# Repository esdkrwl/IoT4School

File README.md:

# IoT4School 2.0
Eine exemplarische Internet of Things Infrastruktur für den Einsatz im Informatikunterricht.

Die größten Änderungen zur Version 1.0:
- Verwendung von Micropython (basierend auf Python 3.4) anstatt Arduino (C++)
- Verwendung eines modularen Stecksystems auf Basis des Evaluationsboards Wemos D1 (ESP8266)
- Blockbasierte Einrichtung und Programmierung der Module mittels BIPES

Hardwarevoraussetzungen:
- Raspberry Pi 3b mit einer mindestens 16GB großen microSD Karte (Raspberry Pi OS: Buster)
  - Möglicherweise auch kompatibel zum Raspberry Pi 4, jedoch nicht getestet
- Ein WLAN-Router zum Empfangen und Versenden von Netzwerkpaketen
- [Wemos D1 mini][1] Mikrocontroller sowie (Wemos-kompatible) [Shields][2]

Um das Projekt IoT4School 2.0 nutzen zu können, müssen folgende Anleitungen nach Reihenfolge durchgeführt werden:  
- [Raspberry Einrichtung mit Image [Für Einsteigende]][3] **ODER** [Raspberry Einrichtung ohne Image [Für erfahrene Anwendende]][4]
- [Wemos D1 Mini Ersteinrichtung und Konfiguration][5]
- [Einführung in das blockbasierte Programmieren mit BIPES und Node-RED][6]

Zusätzlich werden den Entwickelnden zur Erweiterung der IoT4School-Infrastruktur folgende Anleitungen zur Verfügung gestellt:
- [Blöcke für IoT4School entwickeln und einbinden][7]
- [Anpassungen an der Micropython-Firmware vornehmen][8]

Weitere Informationen zum Projekt sind im [Wiki](https://github.com/esdkrwl/IoT4School/wiki) zu finden.

[1]: https://www.wemos.cc/en/latest/d1/d1_mini.html
[2]: https://www.wemos.cc/en/latest/d1_mini_shield/index.html
[3]: https://github.com/esdkrwl/IoT4School/wiki/Raspberry-Pi-Einrichtung-mit-Image
[4]: https://github.com/esdkrwl/IoT4School/wiki/Raspberry-Pi-Einrichtung-ohne-Image
[5]: https://github.com/esdkrwl/IoT4School/wiki/Wemos-D1-mini-(ESP8266)-Einrichtung
[6]: https://github.com/esdkrwl/IoT4School/wiki/Einf%C3%BChrung-in-das-blockbasierte-Programmieren-mit-BIPES-und-Node-RED
[7]: https://github.com/esdkrwl/IoT4School/wiki/Erstelle-IoT4School-2.0-Bl%C3%B6cke
[8]: https://github.com/esdkrwl/IoT4School/wiki/Erzeugen-einer-eigenen-MicroPython-Firmware

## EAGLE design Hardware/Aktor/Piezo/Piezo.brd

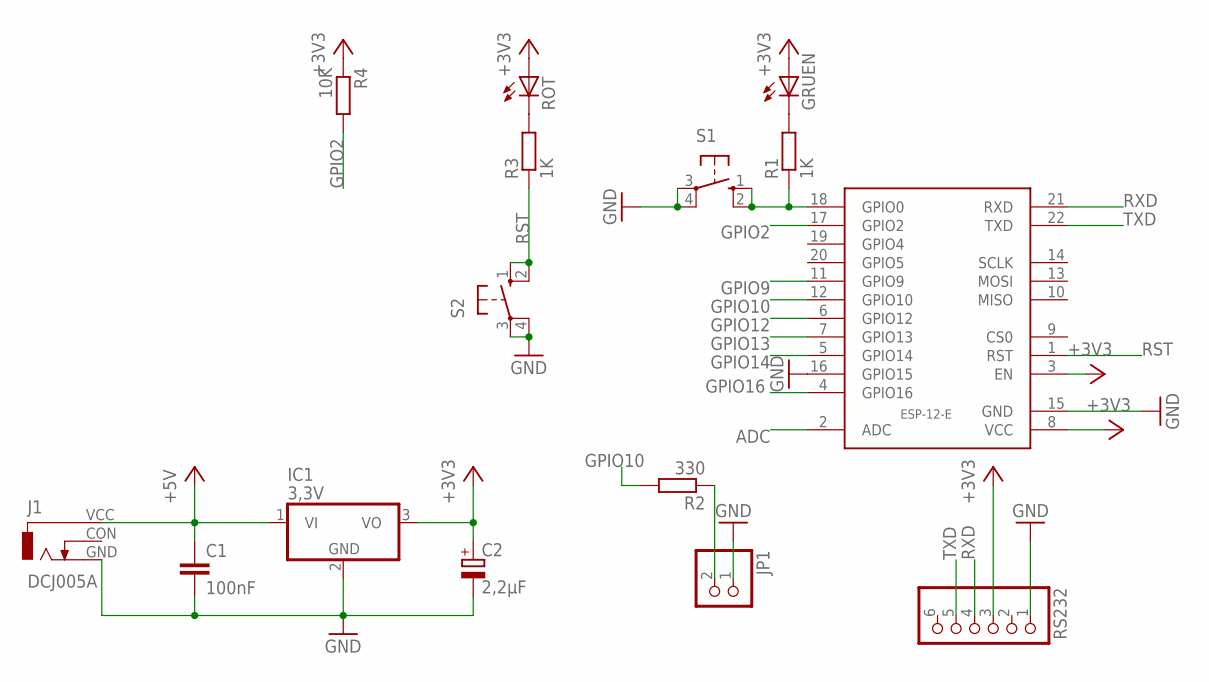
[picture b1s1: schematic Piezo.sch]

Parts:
C1: 100nF; C050-030X075
C2: 2,2µF; E2,5-6
GRUEN: LED5MM
IC1: 3,3V; TO220V
J1: DCJ005A; DC005A
JP1: PINHD-1X2; 1X02
R1, R3: 1K; 0207/10
R2: 330; 0207/10
R4: 10K; 0207/10
ROT: LED5MM
RS232: PINHD-1X6; 1X06
S1, S2: 10-XX; B3F-10XX
U$1: ESP-12-E

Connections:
+3V3: C2.+, GRUEN.A, IC1.3 (VO), R4.1, ROT.A, RS232.3, U$1.3 (EN), U$1.8 (VCC)
+5V: C1.1, IC1.1 (VI), J1.VCC (1)
ADC: U$1.2 (ADC)
GND: C1.2, C2.-, IC1.2 (GND), J1.GND (3), JP1.1, RS232.1, S1.3, S1.4 (P1), S2.3, S2.4 (P1), U$1.15 (GND), U$1.16 (GPIO15)
GPIO2: R4.2, U$1.17 (GPIO2)
GPIO9: U$1.11 (GPIO9)
GPIO10: R2.2, U$1.12 (GPIO10)
GPIO12: U$1.6 (GPIO12)
GPIO13: U$1.7 (GPIO13)
GPIO14: U$1.5 (GPIO14)
GPIO16: U$1.4 (GPIO16)
unnamed: R1.1, S1.1 (S), S1.2 (S1), U$1.18 (GPIO0)
unnamed: JP1.2, R2.1
unnamed: GRUEN.K (C), R1.2
unnamed: R3.2, ROT.K (C)
RST: R3.1, S2.1 (S), S2.2 (S1), U$1.1 (RST)
RXD: RS232.4, U$1.21 (RXD)
TXD: RS232.5, U$1.22 (TXD)

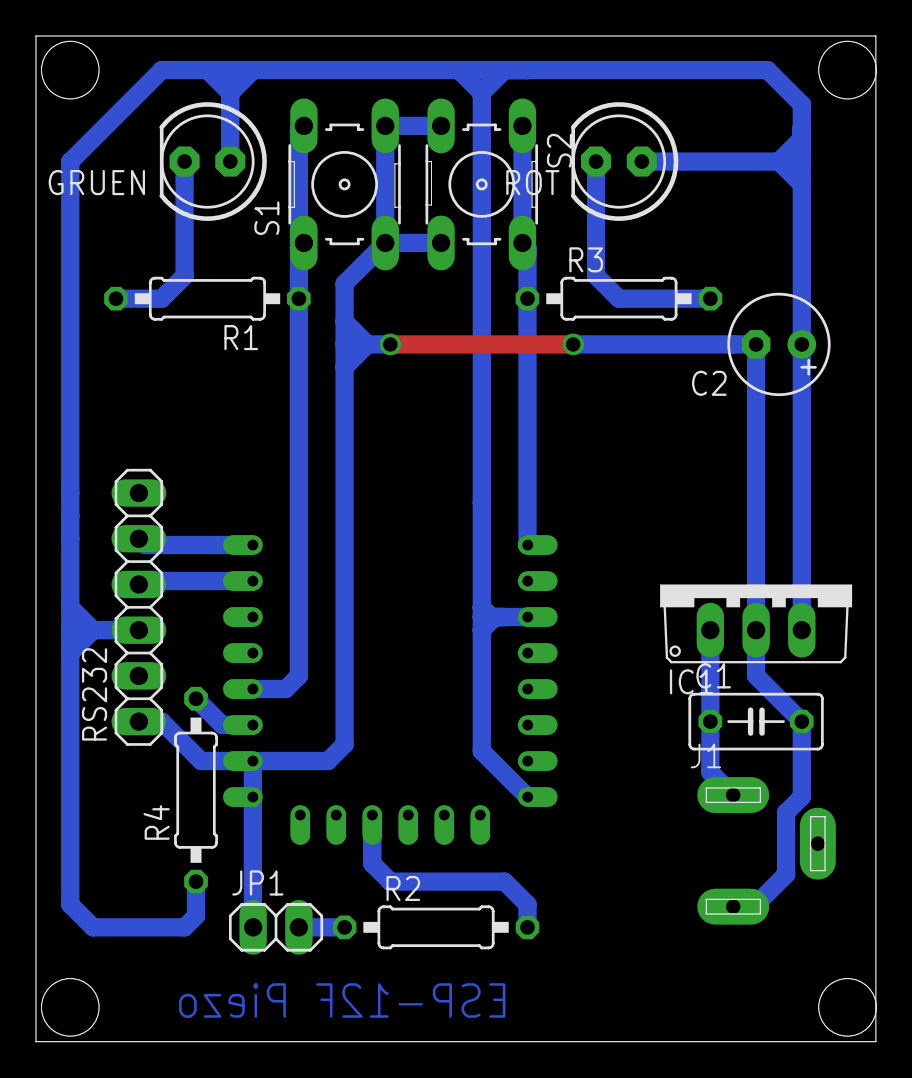
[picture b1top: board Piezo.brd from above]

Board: 2 copper layers, 46.7 x 55.9 mm, 15 parts (1 on the bottom side), 12 nets.

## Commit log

2017-03-04 Sensor, Aktor und Status Node initial commit
2017-03-04 README update
2017-03-04 gitignore zugefügt
2017-03-04 python client zugefügt
2017-03-04 git ignore geupdated
2017-03-04 MQTT gerüst
2017-03-04 unnötigen Ordner gelöscht
2017-03-04 Datei nun an einem besseren ort
2017-03-04 node mit json parser inklusive
2017-03-04 Ordner umbenannt
2017-03-04 DB Zugriffe reduziert - Code an einigen Stellen gekürzt
2017-03-05 Blueprint mit OTA Unterstützung
2017-03-05 PyCharm Projektordner entfernt
2017-03-05 gitignore update
2017-03-05 Sensor Node soweit fertig. Feld für optinalen Namen ergänzt. JSON Parser über Checkbox optinal
2017-03-05 Aktor-Node fertig. Neues Menü mit neuen Icons. JSON Checkbox prüft, ob Ausgabe im JSON Format vorliegt, bevor versendet wird
2017-03-05 Update saymyname.py
    aktuator in aktor umbenannt
2017-03-05 Set theme jekyll-theme-tactile
2017-03-05 JSON Parsing eingebaut
2017-03-05 Aktor Node fügt automatisch Datenidentifier hinzu
2017-03-05 saymyname schickt identifier name mit weg, damit die clients die daten besser parsen können
2017-03-06 identifier name wird korrekt ausgewertet und entsprech des inhaltes topic angepasst. aww yeah
2017-03-06 groß/kleinschreibung
2017-03-06 Ordnerstruktur geändert und Node-Red Beispiele
2017-03-06 systemd Skript für die Namensvergabe
2017-03-06 DB Einträge auf nginx Server anzeigen
2017-03-08 Verbindungsabfragen in den Blueprint eingebaut Erster Code für Poti TODO: toCharArray durch snprintf ersetzen TODO: Python Client muss reconnect handeln
2017-03-08 Neuer Blueprint - reconnect mit Python abgesprochen
2017-03-08 reconnect callback eingebaut
2017-03-08 neuer Blueprint
2017-03-09 -JSON Dekoder sperrt nicht mehr, falls Key nicht vorhanden oder kein JSON vorliegt. -Buffer läuft nicht mehr voll
2017-03-09 neue Poti Software. BUG: Verliert zu Beginn Verbindung zum Broker!!!
2017-03-09 DC Bug behoben - Client hat versucht mit leerem Topic zu publishen
2017-03-09 Eclipse Projekt
2017-03-09 Zur Hölle damit..
2017-03-09 gitignore angepasst
2017-03-10 Blueprint_v3: v2 mit WiFiManager
2017-03-11 Webserver wird nun auch gestartet, falls die Verbindung zum Broker nicht aufgebaut werden kann
2017-03-12 LDR Sensor mit DeepSleep
2017-03-17 erste version led controller
2017-03-17 Beispiele zugefügt
2017-03-18 Einstellungen zu verschiedenen Nodes Anleitung HTML Page
2017-03-19 Multiuser Support
2017-03-19 Update nodered5.service
    typo
2017-03-19 Update Aktor Firmware
2017-03-19 Update Wetter_Beispiel
2017-03-20 Update Skript
2017-03-20 nginx update
2017-03-20 aufräumen
2017-03-20 Update esp.js
    Bug behoben, der Fehler auslöst, wenn sowohl Sensor Node als auch Aktor Node Json parsen
2017-03-20 functions
2017-03-20 portweiterleitung
2017-03-21 Create info
2017-03-21 neue Nodes version
2017-04-09 Button mit 3 Click Events zugefügt
2017-04-09 Buttonkonfig erweitert
2017-04-10 -Blueprint in blockierender Schleife bis neuer Name erhalten. Sendet dort alle 5 Sekunden Status. -saymyname hat nun auch callback für aktoren erhalten TODO: regelmäßig prüfen, ob Verbindung zum Brok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
2017-04-27 Schaltpläne für Button und Mikrofon
2017-04-30 cfg zugefügt
2017-04-30 config Datei
2017-04-30 button gelöscht
2017-04-30 OTA vong niceigkeit verbessert
2017-04-30 OTA Fix
2017-04-30 OTA läuft nun auch bei den generic modulen
2017-05-01 neue gute Firmware
2017-05-02 pub/TYP/NAME/SUFFIX
2017-05-02 RGB zu HSL und umgekehrt
2017-05-02 Steckdose kompatibel zum lampenprotokoll
2017-05-02 RGB-Code mit Helligkeitsstufen
2017-05-02 neue Version nodes
2017-05-03 str bug behoben
2017-05-03 HSV statt HSL
2017-05-04 yeelight wrapper
2017-05-04 clapSensor - jedoch HW fürn arsch
2017-05-04 Wrapper nun zur DB kompatibel
2017-05-05 Bugfixes
2017-05-07 html der neuen funktionsnodes
2017-05-07 js der neuen funktionsnodes
2017-05-08 Revert "neue nodes version"
    This reverts commit a6e699a07604283c4ffcef95f6d65c5ef9c80e47.
2017-05-08 revert revert
2017-05-09 windows installer
2017-05-09 kosmetik
2017-05-09 Source PIR Sensor - buggy shit.
2017-05-09 immer noch verbugt..
2017-05-10 Weder Soft- noch Hardware waren verbugt.. es war mein Hirn
2017-05-10 Interrupt irgendwie träge
2017-05-10 klatsch sensor - interrupts sind kacke
2017-05-10 Wetterstation Firmware
2017-05-10 alte Firmware gelöscht
2017-05-11 onStatus zugefügt
2017-05-11 irgendwas
2017-05-11 tooooooooooooooooooooogle wtf?!
2017-05-18 Smart-Button final
2017-05-18 PIR final
2017-05-18 Clap Sensor Final
2017-05-18 wetterstation final
2017-05-18 update wetterstation node
2017-05-18 klopfer raus geworfen
2017-05-18 kp was sich geändert hat
2017-05-19 final rgb
2017-05-19 Steckdose final
2017-05-19 Blaupause final
2017-05-19 final nodes
2017-05-20 alte nodes rausgeworfen
2017-05-20 Fotos
2017-05-20 alte Boards rausgeworfen
2017-05-20 test commit nach neuem repo namen
2017-05-30 Webseite final
2017-05-30 MQTT DB final
2017-06-01 mini fix
2017-06-02 wrapper final
2017-06-03 wetterstation vor overflow gerettetetet
2017-06-05 final saymyname
2017-06-06 änderungen an einigen kommentaren
2017-06-08 nur noch relative urls NICE
2017-06-08 direktlink zum dashboard geht doch nicht..
2018-07-17 Schaltpläne update
2018-07-17 Firmware zugefügt
    Magnetschalter und Barometer
2018-07-18 Firmware Servomotor zugefügt
2018-07-27 Update Service_einrichten
2018-07-28 Update RGB-Controller AP und Binaries
2018-07-28 Update Binaries
2018-07-28 Steckdose Binaries Update
2018-07-28 Klatsch Binaries update
2018-07-28 Magnetschalter 2018 Binaries Update
2018-07-28 und zugefügt
2018-07-28 PIR 2018 Binaries
2018-07-28 Smart-button 2018 bins
2018-07-28 zufügen vergessen..
2018-07-28 Bodensensorzeug zugefügt
2018-07-28 flashtool zum flashen
2018-07-28 die miesesten 4 scheiß stunden in meinem scheiß leben
2018-07-28 damit git die fresse hält
2018-07-28 neuste Nodes
2018-07-28 neuste Version nodes
2018-07-30 Update Regen/Bogensensor Firmware + neue Binaries
2021-10-13 Entferne Legacy Ordner zur Vorbereitung neuer Ordnerstruktur
2021-10-13 Initialer Commit für IoT 2.0
2021-10-13 Update .gitignore
    uff, .xml nicht ignorieren plz
2021-10-13 Vorher ignorierte .xml Dateien zum Repo hinzufügen
2021-10-13 mosquitto.conf hinzugefügt
2021-10-14 node_module-Ordner hinzugefügt
    Die Docker-Instanzen verweisen auf diesen Ordner. Die Installation der iot4school nodes schlägt fehl, wenn der Ordner nicht vorhanden ist.
2021-10-15 Update README.md
    Verlinkung zum Wiki
2021-10-15 main.py Testzeilen entfernt
    Testzeilen für den Motor-Aktor wurden versehentlich mitcommited
2021-10-17 [Kritisch] Resetloop Fix in network_manager
    Variablen-Zuweisung der internen LED (GPIO2) im Frozen Bytecode-Teil wohl problematisch. (Nicht eingefroren tritt der Fehler nicht auf...) Nun direktes Ansprechen der internen LED innerhalb des netwo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
2021-10-17 Kleiner LED-Fix network-manager
    Wenn über den Zugriffspunkt-Modus eine erfolgreiche Verbindung zum Netzwerk hergestellt wurde, fehlte das visuelle Feedback in Form einer eingeschalteten LED.
2021-10-17 Update README.md
    Beschreibung, wie das Projekt genutzt werden kann, zur README.md hinzugefügt
2021-10-17 Update README.md
    Verweis Entwickler Erweiterung der Infrastruktur hinzugefügt
2021-10-24 Bug Fix RGB Helligkeitsberechnung
    Wenn als Helligkeit 100 übergeben wurde, waren die maximal möglichen Werte für Rot, Grün und Blau jeweils nur 100, was nicht der maximal möglichen Helligkeit der LEDs entspricht (255 ist max)
2021-10-24 Fix Berücksichtigung des aktuellen Helligkeitswert beim Setzen der Farbe
    Fehlerhaftes Verhalten wurde gefixt, wenn z.B. Helligkeit vorher auf 1% gesetzt wurde und im Anschluss der Maximalwert für alle Farben (255, 255, 255) angegeben wurde. Helligkeit verhält sich nun rel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
2021-10-24 Anpassungen an Helligkeitsfunktion
    Unterscheidung alle LED vs LED-Index in brightness-Funktion.
    Notwendig, da ansonsten alle LEDs leuchten, wenn nur für ein LED-Index eine Farbe angegeben wurde.
    (Angabe des LED-Index für Helligkeit als mögliches TODO für den BIPES Block)
2021-10-24 ufff
    IndexError: list index out of range blaaah
2021-10-27 MQTT Publish Block kleiner Fix
    - Leerzeilen in zwei Modulen entfernt
    - MQTT Publish Block hatte eine Standard-Option zu viel
2021-10-31 [FIX] total_click-Counter bei Klick-Aktionen
    - Double-Klick inkrementiert nun richtig um 2 Klicks
    - Nach Loslassen des Buttons wird nicht mehr fälschlicherweise ein Klick gezählt
2021-10-31 Fix Handling DHT22
    - Delay beim Messen für DHT22 eingebaut, da Sample Rate nur bei 0.5
    - Doppelte Abfrage von self.enabled entfernt, da unnötig
2021-11-08 Zähler Reset vereinheitlichen
    Werte des Schlüssels können nun, wie auch beim PIR, beliebig sein.
2021-11-10 Richtige Quellenangabe
    Alte Quelle war Firmware für Motor Shield, nicht die Library
2021-11-12 [FIX] brake() -Funktion setzt nun Geschwindikgeit auf 0
    Bremsen der Motoren hat die internen Geschwindigkeits-Indikatoren nicht auf 0 gesetzt. So hat eine Statusabfrage nach Abbremsung nicht den wirklichen Zustand widergespiegelt.
2022-06-03 Fix für den BIPES-Patcher
    Die Toolbox wurde nicht mehr richtig gepatcht. Neue Suchmarke für den Insert ausgewählt.
2022-06-12 Weitere Kompatibilitäts-Anpassungen BIPES-Patcher
    - Patcher kompatibel zur aktuellsten, auf dem master-Branch veröffentlichten Version von BIPES (Commit: a16f66e76d5827f840454eaf9760b2f379e10d1b vom 09. April)
    - Kompatibilität zum Multi-Projekt-Support hergestellt
    - Dateibenennung im "Files"-Tab standardmäßig main.py
2022-06-25 Umfassende Änderungen am BIPES Patcher
    - Patcher bezieht nun Dateien aus einem angepassten Forks des BIPES-Repos
    - Patcher prüft auf Internetverbindung
    - Das Aktualisieren von BIPES kann nun automatisch (durch Ablöschen und dem neuen Herunterladen des Ordners) angestoßen werden
